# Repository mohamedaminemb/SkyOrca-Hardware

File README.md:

# SkyOrca — Quadcopter Drone Hardware

> **SkyOrca** is a fully custom quadcopter drone system designed from scratch at ENSI (Tunisia), in partnership with [LAB619 Engineering & Consulting Services](https://lab619.tn). This repository contains the complete hardware design — schematics, PCB layouts, Gerber files, and BOMs — for all three boards.

---

## System Overview

SkyOrca is built around three custom PCBs that together form a complete drone flight & control chain:

| Board | Role | MCU | Dimensions |
|-------|------|-----|------------|
| **SkyOrcaFC** | Flight Controller | STM32F405RGTx @ 168 MHz | 60 × 50 mm |
| **SkyOrcaTX** | Remote Controller (Transmitter) | ATmega328P-P @ 8 MHz | 50 × 35 mm |
| **SkyOrcaRX** | Communication Module (Receiver) | ATmega2560-16A @ 8 MHz | 30 × 25 mm |

---

## Repository Structure

```
SkyOrca-Hardware/
├── hardware/
│   ├── SkyOrcaFC/              # Flight Controller Board
│   │   ├── kicad/              # KiCad project files (.kicad_pro, .kicad_sch, .kicad_pcb)
│   │   ├── gerbers/            # Production Gerber files + drill files
│   │   └── bom/                # Bill of Materials (CSV + interactive iBOM)
│   ├── SkyOrcaTX/              # Remote Controller Board
│   │   ├── kicad/
│   │   ├── gerbers/
│   │   └── bom/
│   └── SkyOrcaRX/              # Receiver Module
│       ├── kicad/
│       └── bom/
├── docs/
│   ├── images/                 # architecture_drawio.png + board renders
│   ├── SkyOrcaFC.md
│   ├── SkyOrcaTX.md
│   ├── SkyOrcaRX.md
│   └── design_decisions.md
├── .gitignore
├── LICENSE
└── README.md
```

---

## Board Details

### SkyOrcaFC — Flight Controller

The brain of the drone. Reads all sensors, runs stabilization algorithms, and drives the four ESCs.

**Key components:**
- **MCU:** STM32F405RGTx — Cortex-M4F @ 168 MHz, hardware FPU (quaternion math, sensor fusion at 400 Hz)
- **IMU:** MPU-6000 — SPI @ 20 MHz, DMA-triggered via EXTI interrupt, 400 Hz control loop
- **Barometer:** MS5611-01BA — 10 cm altitude resolution, I²C shared bus
- **Magnetometer:** HMC5883L — I²C shared bus
- **GPS:** u-blox MAX-M10S — multi-constellation (GPS/GLONASS/Galileo/BeiDou), UART
- **Flash:** W25Q128JVS — 128 Mbit, SPI @ 133 MHz, flight data logging
- **Power:** Dual TPS5430DDA buck converters (12V→5V and 12V→3.3V)
- **PCB:** 4-layer, 60×50 mm (rev 2), manufactured by JLCPCB

> **PCB revisions:** The first revision (50×50 mm) was redesigned due to GPS/DC-DC proximity and thermal density issues. See [`docs/SkyOrcaFC.md`](docs/SkyOrcaFC.md) for the full analysis.

---

### SkyOrcaTX — Remote Controller

Hand-held transmitter reading pilot inputs and displaying telemetry.

**Key components:**
- **MCU:** ATmega328P-P @ 8 MHz (DIP-28)
- **Radio:** XBee 802.15.4 module — bidirectional, up to 1.6 km range, UART interface
- **Inputs:** 2× analog joysticks (4-axis), 2 buttons
- **Display:** OLED (I²C) — battery level, altitude, RSSI
- **Power:** TPS5430DDA buck converter (7.4V→3.3V)
- **PCB:** 4-layer, 50×35 mm

---

### SkyOrcaRX — Receiver Module

On-board radio bridge between the XBee link and the Flight Controller.

**Key components:**
- **MCU:** ATmega2560-16A @ 8 MHz — 4 hardware UARTs (radio / FC link / debug / spare)
- **Radio:** XBee 802.15.4 module
- **Interface to FC:** UART2 → `IBUS_RX_MCU` on SkyOrcaFC
- **Power:** 3.3V supplied directly by SkyOrcaFC
- **PCB:** 4-layer, 30×25 mm

---

## Inter-Board Communication

| Link | Signal | Protocol |
|------|--------|----------|
| TX → RX (commands) | XBee RF 2.4 GHz | IEEE 802.15.4 |
| RX → FC (commands) | `UART2` → `IBUS_RX_MCU` | UART |
| FC → TX (telemetry) | `MSP_TX_MCU` → XBee → `RXD_MCU` | UART + XBee RF |
| FC → ESC 1–4 | `Signal_ESC1–4` | PWM |

All three boards share a **3.3V logic level**, eliminating any need for level shifters between STM32 and ATmega devices.

---

## Getting Started

### Prerequisites

- [KiCad 9.0.x](https://www.kicad.org/download/) to open and edit the project files

### Opening a Project

```bash
git clone https://github.com/mohamedaminemb/SkyOrca-Hardware.git
cd SkyOrca-Hardware

# Open the Flight Controller in KiCad
kicad hardware/SkyOrcaFC/kicad/flightcontrolerPCB.kicad_pro
```

### Ordering PCBs (SkyOrcaFC)

Upload `hardware/SkyOrcaFC/gerbers/gerbers_production.zip` to [JLCPCB](https://jlcpcb.com):

| Setting | Value |
|---------|-------|
| Layers | **4** |
| PCB thickness | **1.6 mm** |
| Surface finish | **HASL (lead-free)** or **ENIG** |
| Min trace/space | **0.15 / 0.15 mm** |

---

## Design Philosophy

This project follows a **hardware/software co-design** methodology. Every component choice is directly motivated by firmware constraints. See [`docs/design_decisions.md`](docs/design_decisions.md) for the full rationale.

---

## Project Context

SkyOrca is a design and development project (PCD) at **ENSI** (École Nationale des Sciences de l'Informatique, Tunisia), developed in the context of Tunisia's first civil drone legislation (Finance Law 2026, Article 135), in collaboration with **LAB619 Engineering & Consulting Services**.

**Team:** Mohamed Amine Embarki · Hamza Soltani  
**Supervisors:** Mme. Chadha Jerad · M. Jawher Mansour (LAB619)  
**Tools:** KiCad 9.0.4 · JLCPCB

---

## License

Hardware designs are released under the **CERN Open Hardware Licence v2 – Strongly Reciprocal (CERN-OHL-S)**.  
See [`LICENSE`](LICENSE) for details.

---

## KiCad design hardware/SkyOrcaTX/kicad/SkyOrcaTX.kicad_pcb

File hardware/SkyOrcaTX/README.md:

# SkyOrcaTX — Remote Controller Board

> Full design documentation: [`docs/SkyOrcaTX.md`](../../docs/SkyOrcaTX.md)

## Contents

```
SkyOrcaTX/
├── kicad/
│   ├── SkyOrcaTX.kicad_pro
│   ├── SkyOrcaTX.kicad_sch
│   ├── SkyOrcaTX.kicad_pcb
│   └── schematic.pdf
└── bom/
    └── ibom.html                       # Interactive BOM (open in browser)
```

## Quick Specs

| Parameter | Value |
|-----------|-------|
| MCU | ATmega328P-P @ 8 MHz |
| Dimensions | 50 × 35 mm |
| Layers | 4 |
| Power input | 7.4V (LiPo 2S) |
| Radio | XBee 802.15.4 (up to 1.6 km) |
| Revision | 1 |

## Ordering

No Gerber zip is included in this release — contact the project team or generate from the KiCad project. Use the same JLCPCB 4-layer settings as SkyOrcaFC.

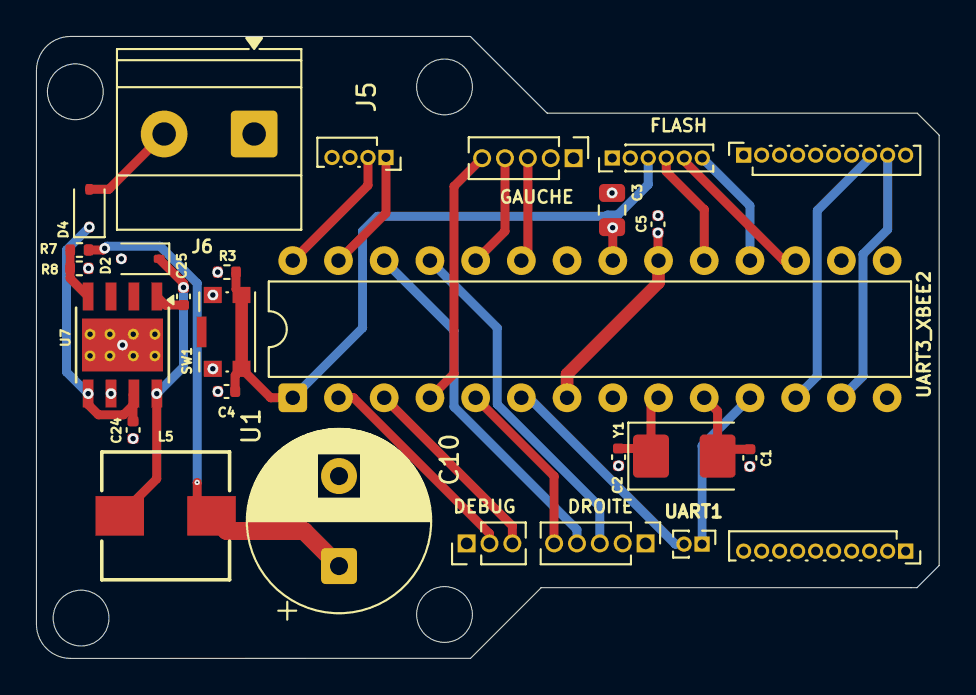
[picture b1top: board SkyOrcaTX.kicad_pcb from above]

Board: 4 copper layers, 50.2 x 34.6 mm, 27 parts (0 on the bottom side), 28 nets.

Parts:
C1, C2: 20pF; C_0402_1005Metric
C3: 100 nF; C_0805_2012Metric
C4: 100nF; C_0402_1005Metric
C5: 100 nF; C_0402_1005Metric
C10: 560uF; CP_Radial_D10.0mm_P5.00mm
C24: 4.7 uF; C_0402_1005Metric
C25: 10nF; C_0402_1005Metric
D2: MRBS340; D_SOD-323
D4: D_Schottky; D_SOD-323
DEBUG: Conn_01x03_Pin; PinHeader_1x03_P1.27mm_Vertical
DROITE: Conn_01x05_Pin; PinHeader_1x05_P1.27mm_Vertical
FLASH: Conn_01x06_Pin; PinHeader_1x06_P1.00mm_Vertical
GAUCHE : Conn_01x05_Pin; PinHeader_1x05_P1.27mm_Vertical
J5: Conn_01x04_Pin; PinSocket_1x04_P1.00mm_Vertical
J6: Screw_Terminal_01x02; TerminalBlock_Phoenix_MKDS-1,5-2_1x02_P5.00mm_Horizontal
L5: 10 uH; WE-HCI_7040
R3: 10 k; R_0402_1005Metric
R7: 10 K; R_0402_1005Metric
R8: 5.9 K; R_0402_1005Metric
SW1: SW_Push; SW_Push_1P1T-SH_NO_CK_KMR2xxG
U1: ATmega328P-P; DIP-28_W7.62mm
U7: TPS5430DDA; TI_SO-PowerPAD-8_ThermalVias
UART1: Conn_01x02_Pin; PinHeader_1x02_P1.00mm_Vertical
UART3_XBEE1, UART3_XBEE2: Conn_01x10_Pin; PinSocket_1x10_P1.00mm_Vertical
Y1: 8 MHZ; Crystal_SMD_5032-2Pin_5.0x3.2mm

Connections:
+3.3V: C3.1, C5.1, DROITE.2, FLASH.2, GAUCHE.2, J5.3, R3.2, U1.7 (VCC), U1.20 (AVCC), U1.21 (AREF), UART3_XBEE2.10
GND: C1.1, C2.1, C3.2, C4.2, C5.2, C10.2, C24.2, D2.2 (A), DEBUG.1, DROITE.1, FLASH.1, GAUCHE.1, J5.4, J6.1, R8.2, SW1.1, U1.8 (GND), U1.22 (GND), U7.6 (GND), U7.9 (GNDPAD), UART3_XBEE2.1
I2C_SCL: J5.2, U1.28 (PC5)
I2C_SDA: J5.1, U1.27 (PC4)
MISO: FLASH.6, U1.18 (PB4)
MOSI: FLASH.5, U1.17 (PB3)
unnamed: C25.1, D2.1 (K), L5.1, U7.8 (PH)
unnamed: D4.2 (A), J6.2
unnamed: U1.6 (PD4), UART1.2
unnamed: U1.11 (PD5), UART1.1
unnamed: C2.2, U1.9 (XTAL1/PB6), Y1.1
unnamed: C1.2, U1.10 (XTAL2/PB7), Y1.2
unnamed: C25.2, U7.1 (BOOT)
unnamed: R7.1, R8.1, U7.4 (VSENSE)
RES: C4.1, FLASH.3, R3.1, SW1.2, U1.1 (~RESET/PC6)
RXD_MCU: DEBUG.2, U1.2 (PD0)
RXD_MCU_xbee: U1.13 (PD7), UART3_XBEE2.9
SCK: FLASH.4, U1.19 (PB5)
SWD: DROITE.5, U1.5 (PD3)
SWG: GAUCHE.5, U1.4 (PD2)
TXD_MCU: DEBUG.3, U1.3 (PD1)
TXD_MCU_xbee: U1.12 (PD6), UART3_XBEE2.8
VIN: C24.1, D4.1 (K), U7.5 (EN), U7.7 (VIN)
VOUT_3.3V: C10.1, L5.2, R7.2
VRXD: DROITE.3, U1.25 (PC2)
VRXG: GAUCHE.3, U1.23 (PC0)
VRYD: DROITE.4, U1.26 (PC3)
VRYG: GAUCHE.4, U1.24 (PC1)

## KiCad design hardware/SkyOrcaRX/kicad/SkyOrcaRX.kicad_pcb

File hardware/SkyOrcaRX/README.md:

# SkyOrcaRX — Receiver / Communication Module

> Full design documentation: [`docs/SkyOrcaRX.md`](../../docs/SkyOrcaRX.md)

## Contents

```
SkyOrcaRX/
├── kicad/
│   ├── SkyOrcaRX.kicad_pro
│   ├── SkyOrcaRX.kicad_sch
│   ├── SkyOrcaRX.kicad_pcb
│   └── schematic.pdf
└── bom/
    (BOM to be exported from KiCad project)
```

## Quick Specs

| Parameter | Value |
|-----------|-------|
| MCU | ATmega2560-16A @ 8 MHz |
| Dimensions | 30 × 25 mm |
| Layers | 4 |
| Power input | 3.3V from SkyOrcaFC |
| Radio | XBee 802.15.4 |
| UARTs | 4 (radio / FC link / debug / spare) |
| Revision | 1 |

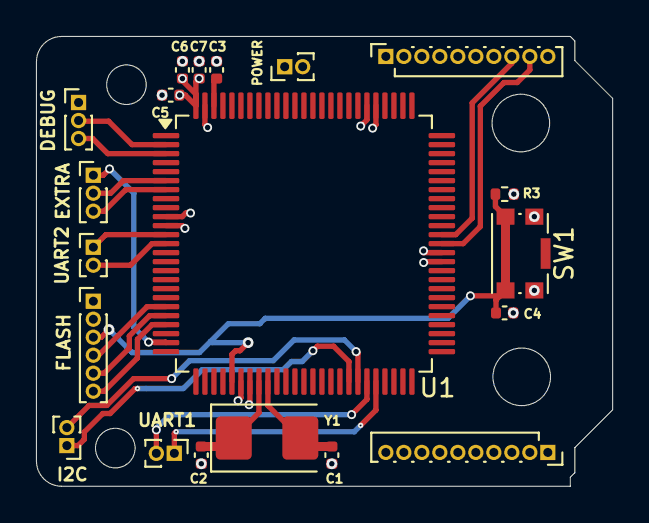
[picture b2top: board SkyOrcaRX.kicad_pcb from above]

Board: 4 copper layers, 32.0 x 25.0 mm, 20 parts (0 on the bottom side), 22 nets.

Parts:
C1, C2: 22pF; C_0402_1005Metric
C3, C5, C6, C7: 100 nF; C_0402_1005Metric
C4: 100nF; C_0402_1005Metric
DEBUG: Conn_01x03_Pin; PinHeader_1x03_P1.00mm_Vertical
EXTRA: Conn_01x03_Pin; PinHeader_1x03_P1.00mm_Vertical
FLASH: Conn_01x06_Pin; PinHeader_1x06_P1.00mm_Vertical
I2C: Conn_01x02_Pin; PinHeader_1x02_P1.00mm_Vertical
POWER: Conn_01x02_Pin; PinHeader_1x02_P1.00mm_Vertical
R3: 10 k; R_0402_1005Metric
SW1: SW_Push; SW_Push_1P1T-SH_NO_CK_KMR2xxG
U1: ATmega2560-16A; TQFP-100_14x14mm_P0.5mm
UART1, UART2: Conn_01x02_Pin; PinHeader_1x02_P1.00mm_Vertical
UART3_XBEE1, UART3_XBEE2: Conn_01x10_Pin; PinSocket_1x10_P1.00mm_Vertical
Y1: 8 MHZ; Crystal_SMD_5032-2Pin_5.0x3.2mm

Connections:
+3.3V: C5.1, C6.1, C7.1, FLASH.2, POWER.1, R3.2, U1.10 (VCC), U1.31 (VCC), U1.61 (VCC), U1.80 (VCC), U1.100 (AVCC), UART3_XBEE2.10
GND: C1.1, C2.1, C3.2, C4.2, C5.2, C6.2, C7.2, DEBUG.1, FLASH.1, POWER.2, SW1.1, U1.11 (GND), U1.32 (GND), U1.62 (GND), U1.81 (GND), U1.99 (GND), UART3_XBEE2.1
GPIO1: EXTRA.2, U1.6 (PE4)
GPIO2: EXTRA.3, U1.7 (PE5)
GPIO3/PWM: EXTRA.1, U1.24 (PB5)
I2C_SCL: I2C.1, U1.43 (PD0)
I2C_SDA: I2C.2, U1.44 (PD1)
MISO: FLASH.6, U1.22 (PB3)
MOSI: FLASH.5, U1.21 (PB2)
unnamed: C3.1, U1.98 (AREF)
unnamed: U1.45 (PD2), UART1.2
unnamed: U1.46 (PD3), UART1.1
unnamed: DEBUG.2, U1.2 (PE0)
unnamed: DEBUG.3, U1.3 (PE1)
unnamed: U1.12 (PH0), UART2.1
unnamed: U1.13 (PH1), UART2.2
unnamed: U1.63 (PJ0), UART3_XBEE2.9
unnamed: U1.64 (PJ1), UART3_XBEE2.8
unnamed: C1.2, U1.34 (XTAL1), Y1.2
unnamed: C2.2, U1.33 (XTAL2), Y1.1
RES: C4.1, FLASH.3, R3.1, SW1.2, U1.30 (~RESET)
SCK: FLASH.4, U1.20 (PB1)

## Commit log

2026-06-01 Rename README_SkyOrcaFC.md to README.md

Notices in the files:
README.md:
License: CERN-OHL-S
